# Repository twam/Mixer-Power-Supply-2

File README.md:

Mixer-Power-Supply-2
===

This repository is part of the USB audio mixer project described on https://www.twam.info/general/building-a-custom-usb-audio-mixer.

It supersedes http://github.com/twam/Mixer-Power-Supply.

## License

[![CC BY-SA 4.0][cc-by-sa-shield]][cc-by-sa]

This work is licensed under a [Creative Commons Attribution-NonCommercial-ShareAlike 4.0 International License][cc-by-sa].

[![CC BY-SA 4.0][cc-by-sa-image]][cc-by-sa]

[cc-by-sa]: http://creativecommons.org/licenses/by-nc-sa/4.0/
[cc-by-sa-image]: https://licensebuttons.net/l/by-nc-sa/4.0/88x31.png
[cc-by-sa-shield]: https://img.shields.io/badge/License-CC%20BY--NC--SA%204.0-lightgrey.svg

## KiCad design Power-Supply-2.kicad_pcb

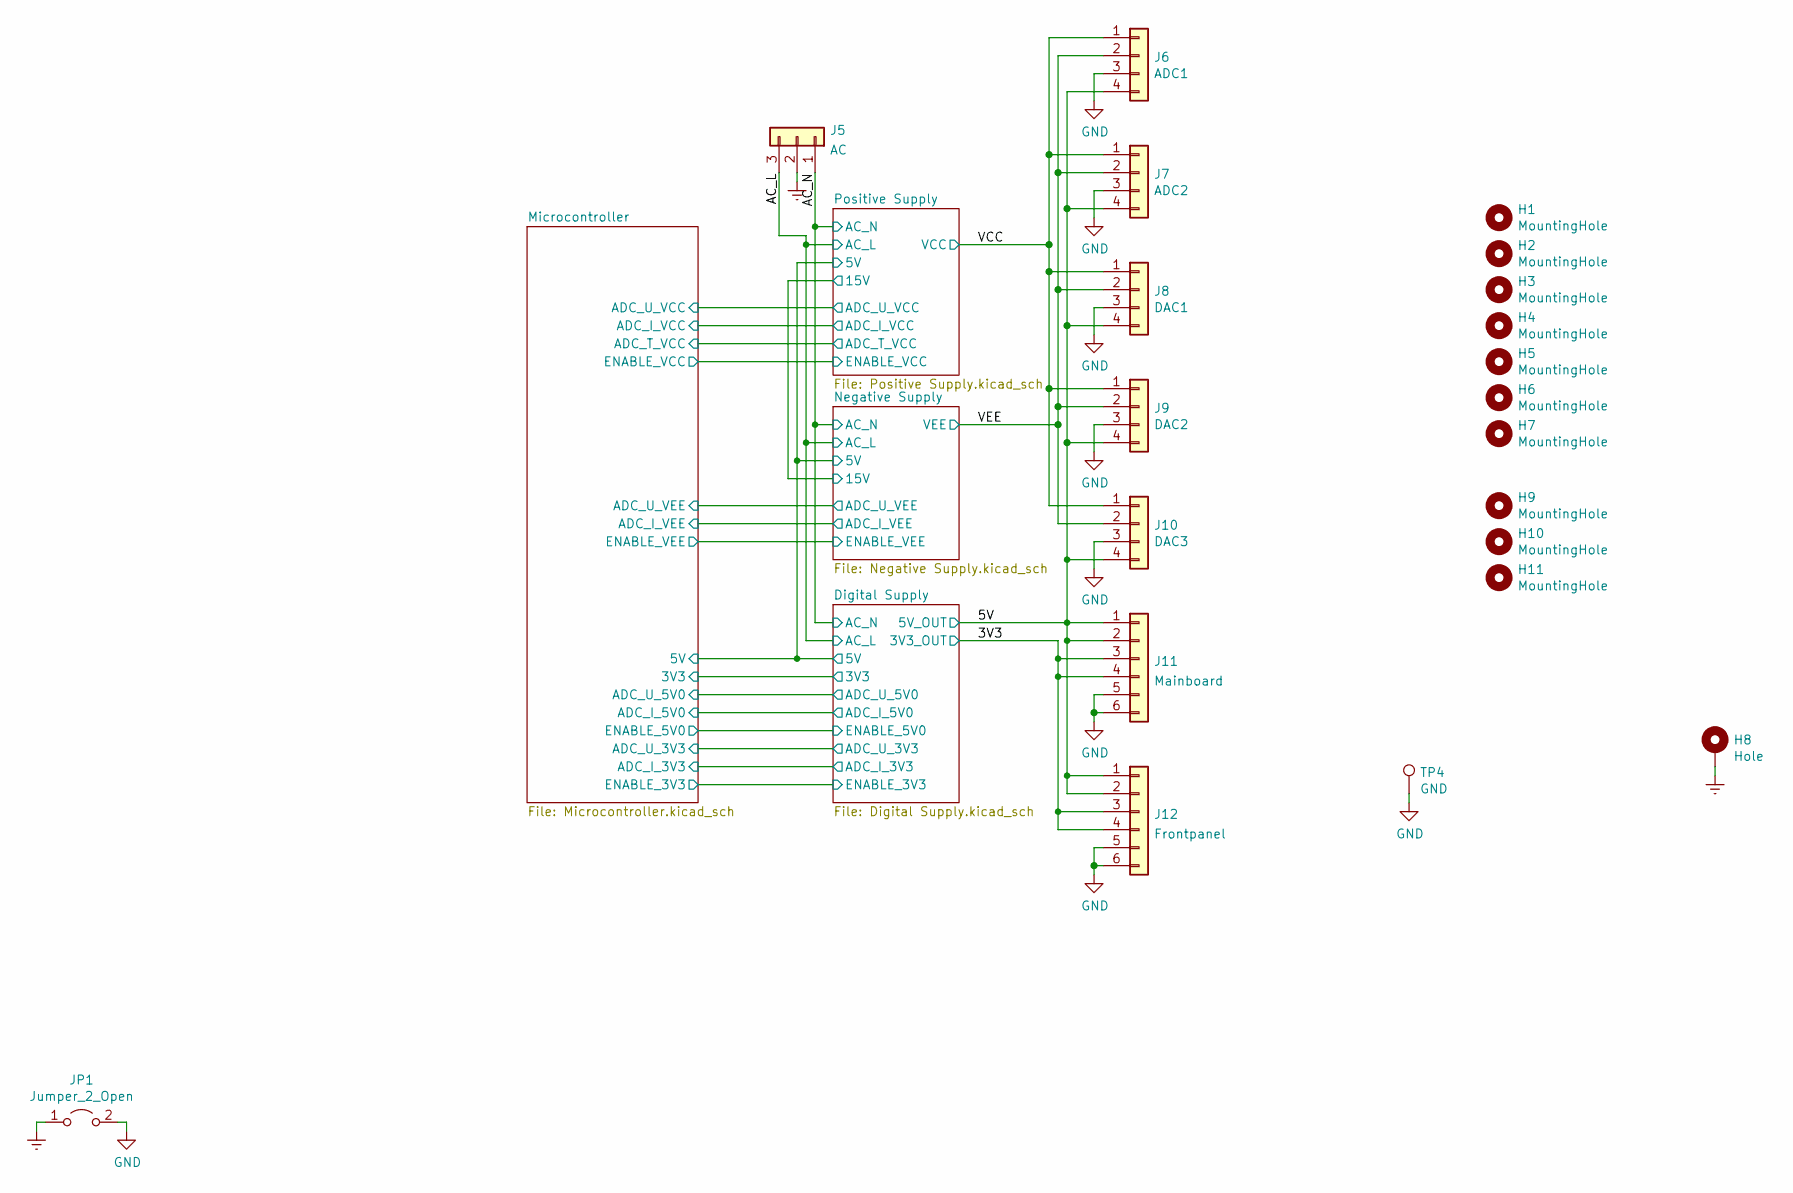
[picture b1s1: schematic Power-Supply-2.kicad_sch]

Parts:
H1, H2, H3, H4, H5, H6, H7: MountingHole; MountingHole_3.2mm_M3_DIN965
H8: Hole; MountingHole_3.2mm_M3_DIN965_Pad
H9, H10, H11: MountingHole; MountingHole_JLCPCB
J5: AC; JST_VH_B3P-VH_1x03_P3.96mm_Vertical
J6: ADC1; JST_VH_B4P-VH_1x04_P3.96mm_Vertical
J7: ADC2; JST_VH_B4P-VH_1x04_P3.96mm_Vertical
J8: DAC1; JST_VH_B4P-VH_1x04_P3.96mm_Vertical
J9: DAC2; JST_VH_B4P-VH_1x04_P3.96mm_Vertical
J10: DAC3; JST_VH_B4P-VH_1x04_P3.96mm_Vertical
J11: Mainboard; JST_VH_B6P-VH_1x06_P3.96mm_Vertical
J12: Frontpanel; JST_VH_B6P-VH_1x06_P3.96mm_Vertical
JP1: Jumper_2_Open; SolderJumper-2_P1.3mm_Open_RoundedPad1.0x1.5mm
TP4: GND; TestPoint_Pad_D2.0mm

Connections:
/3V3: J11.3, J11.4, J12.3, J12.4; also elsewhere on the board
/5V: J6.4, J7.4, J8.4, J9.4, J10.4, J11.1, J11.2, J12.1, J12.2; also elsewhere on the board
/AC_L: J5.3; also elsewhere on the board
/AC_N: J5.1; also elsewhere on the board
/VCC: J6.1, J7.1, J8.1, J9.1, J10.1; also elsewhere on the board
/VEE: J6.2, J7.2, J8.2, J9.2, J10.2; also elsewhere on the board
Earth: H8.1, J5.2, JP1.1 (A)
GND: J6.3, J7.3, J8.3, J9.3, J10.3, J11.5, J11.6, J12.5, J12.6, JP1.2 (B), TP4.1; also elsewhere on the board

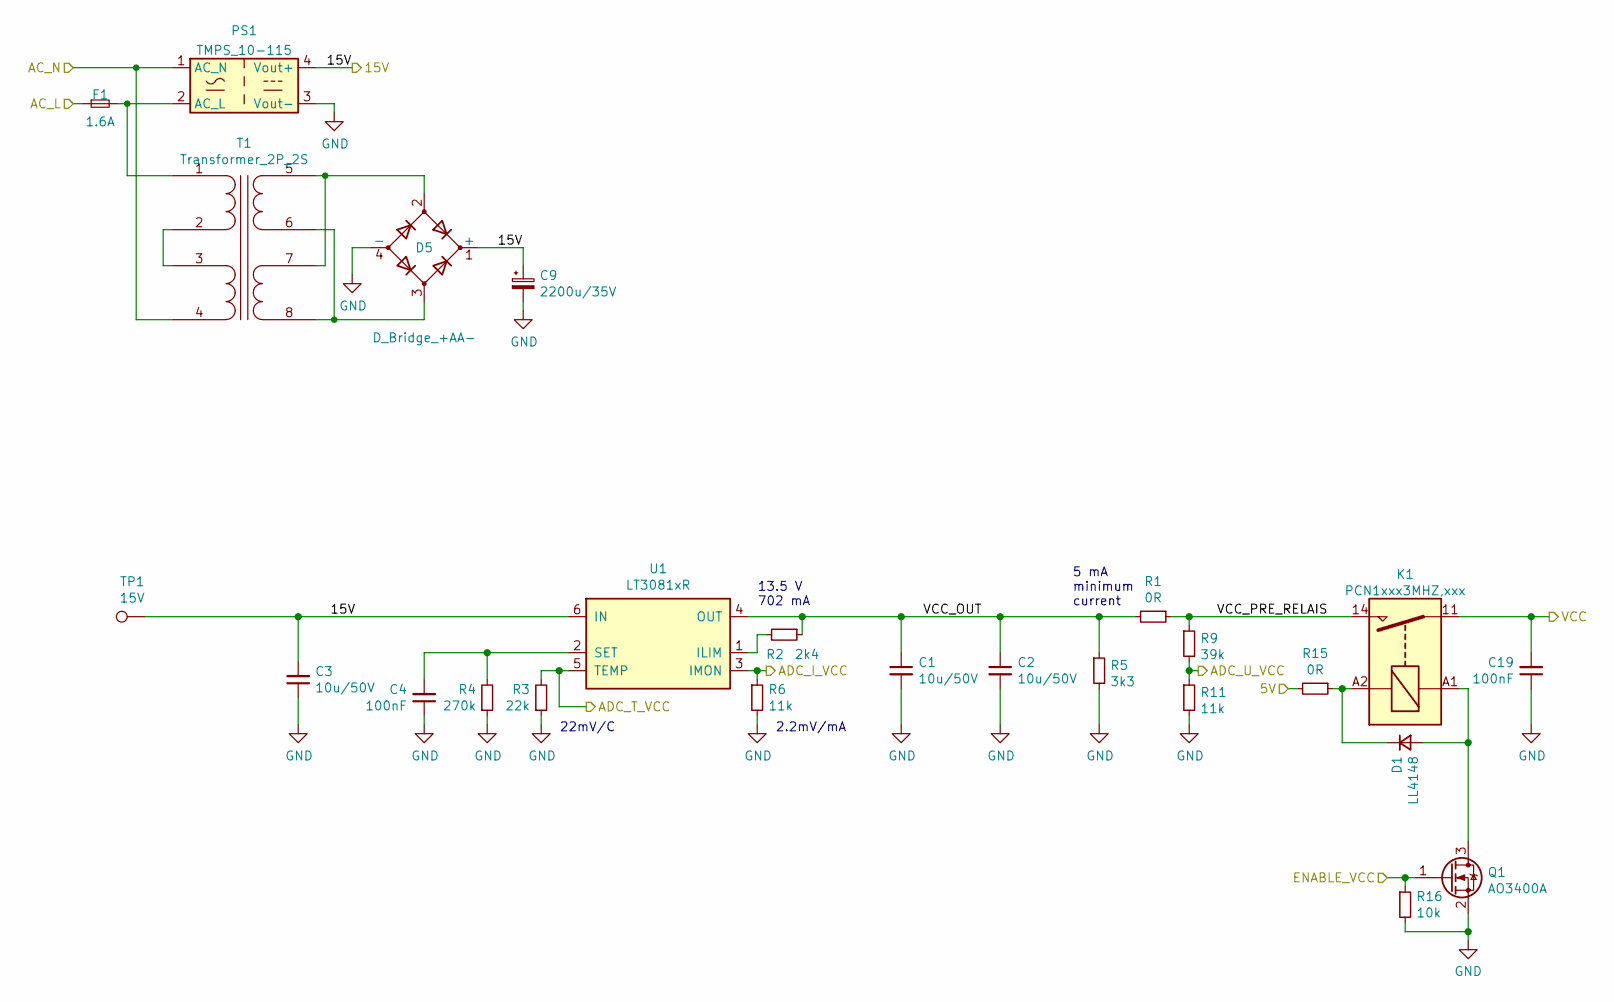
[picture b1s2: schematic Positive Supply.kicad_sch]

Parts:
C1, C2, C3: 10u/50V; C_1206_3216Metric; LCSC C13585
C4, C19: 100nF; C_0603_1608Metric; LCSC C14663
C9: 2200u/35V; CP_Radial_D16.0mm_P7.50mm
D1: LL4148; D_MiniMELF; LCSC C9808
D5: D_Bridge_+AA-; Diode_Bridge_Bourns_CD-HD2xxx
F1: 1.6A; Fuseholder_Cylinder-5x20mm_Schurter_0031_8201_Horizontal_Op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
K1: PCN1xxx3MHZ,xxx
PS1: TMPS_10-115; Converter_ACDC_TRACO_TMPS_10-xxx
Q1: AO3400A; TSOT-23; LCSC C20917
R1, R15: 0R; R_0805_2012Metric; LCSC C17477
R2: 2k4; R_0603_1608Metric; LCSC C22940
R3: 22k; R_0603_1608Metric; LCSC C31850
R4: 270k; R_0603_1608Metric; LCSC C22965
R5: 3k3; R_0805_2012Metric; LCSC C26010
R6, R11: 11k; R_0603_1608Metric; LCSC C25950
R9: 39k; R_0805_2012Metric; LCSC C23153
R16: 10k; R_0603_1608Metric; LCSC C25804
T1: Transformer_2P_2S; Talema_7xxxx_15VA
TP1: 15V; TestPoint_Pad_D2.0mm
U1: LT3081xR; TO-220-7_P2.54x3.8mm_StaggerOdd_Lead5.85mm_TabDown

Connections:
/AC_L: F1.1; also elsewhere on the board
/AC_N: PS1.1 (AC_N), T1.4 (OUT2B); also elsewhere on the board
/Digital Supply/5V: R15.2; also elsewhere on the board
/Microcontroller/ADC_I_VCC: R6.1, U1.3 (IMON); also elsewhere on the board
/Microcontroller/ADC_T_VCC: R3.2, U1.5 (TEMP); also elsewhere on the board
/Microcontroller/ADC_U_VCC: R9.2, R11.1; also elsewhere on the board
/Microcontroller/ENABLE_VCC: Q1.1 (G), R16.1; also elsewhere on the board
/Positive Supply/15V: C3.2, C9.1, D5.1 (+), PS1.4 (Vout+), TP1.1, U1.6 (IN); also elsewhere on the board
/Positive Supply/VCC_OUT: C1.1, C2.1, R1.2, R2.1, R5.1, U1.4 (OUT)
/Positive Supply/VCC_PRE_RELAIS: K1.14, R1.1, R9.1
/VCC: C19.2, K1.11; also elsewhere on the board
GND: C1.2, C2.2, C3.1, C4.1, C9.2, C19.1, D5.4 (-), PS1.3 (Vout-), Q1.2 (S), R3.1, R4.1, R5.2, R6.2, R11.2, R16.2; also elsewhere on the board
unnamed: C4.2, R4.2, U1.2 (SET)
unnamed: D1.1 (K), K1.A2, R15.1
unnamed: D1.2 (A), K1.A1, Q1.3 (D)
unnamed: D5.2, T1.5 (OUT1A), T1.7 (OUT2A)
unnamed: D5.3, T1.6 (OUT1B), T1.8 (OUT2B)
unnamed: F1.2, PS1.2 (AC_L), T1.1 (IN1A)
unnamed: R2.2, U1.1 (ILIM)
unnamed: T1.2 (IN1B), T1.3 (OUT2A)

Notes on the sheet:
2.2mV/mA
5 mA minimum current
22mV/C
13.5 V 702 mA

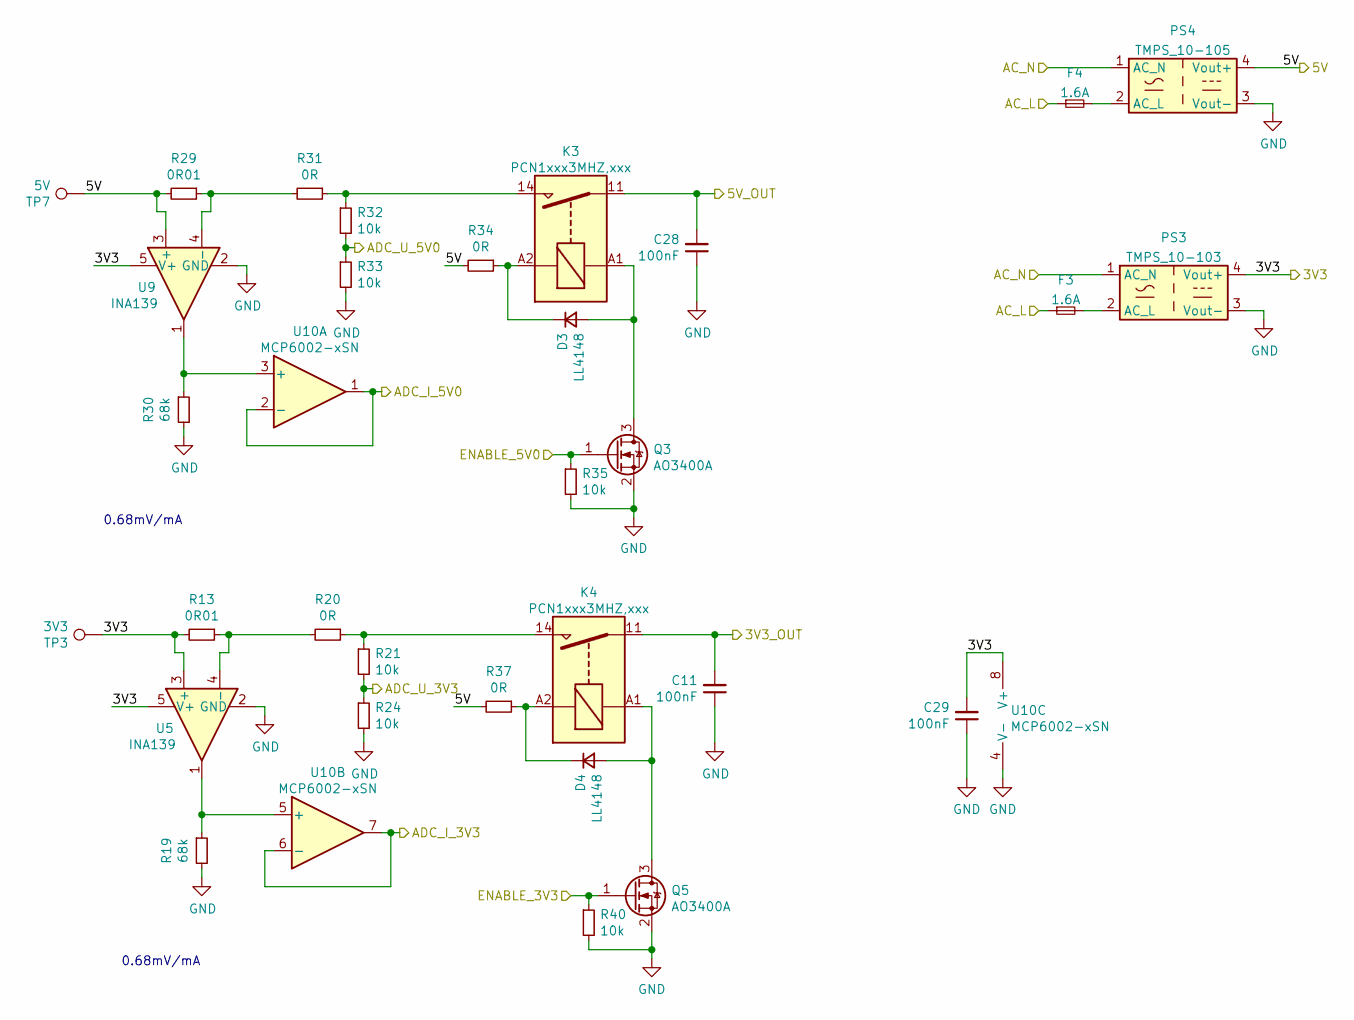
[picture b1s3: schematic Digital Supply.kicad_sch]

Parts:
C11, C28, C29: 100nF; C_0603_1608Metric; LCSC C14663
D3, D4: LL4148; D_MiniMELF; LCSC C9808
F3, F4: 1.6A; Fuseholder_Cylinder-5x20mm_Schurter_0031_8201_Horizontal_Op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
K3, K4: PCN1xxx3MHZ,xxx
PS3: TMPS_10-103; Converter_ACDC_TRACO_TMPS_10-xxx
PS4: TMPS_10-105; Converter_ACDC_TRACO_TMPS_10-xxx
Q3, Q5: AO3400A; TSOT-23; LCSC C20917
R13, R29: 0R01; R_1206_3216Metric; LCSC C308574
R19, R30: 68k; R_0603_1608Metric; LCSC C23231
R20, R31, R34, R37: 0R; R_0805_2012Metric; LCSC C17477
R21, R24, R32, R33, R35, R40: 10k; R_0603_1608Metric; LCSC C25804
TP3: 3V3; TestPoint_Pad_D2.0mm
TP7: 5V; TestPoint_Pad_D2.0mm
U5, U9: INA139; SOT-23-5; LCSC C129947
U10: MCP6002-xSN; SOIC-8_3.9x4.9mm_P1.27mm

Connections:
/3V3: C11.2, K4.11; also elsewhere on the board
/5V: C28.2, K3.11; also elsewhere on the board
/AC_L: F3.1, F4.1; also elsewhere on the board
/AC_N: PS3.1 (AC_N), PS4.1 (AC_N); also elsewhere on the board
/Digital Supply/3V3: C29.2, PS3.4 (Vout+), R13.2, TP3.1, U5.3 (+), U5.5 (V+), U9.5 (V+), U10.8 (V+); also elsewhere on the board
/Digital Supply/5V: PS4.4 (Vout+), R29.2, R34.2, R37.2, TP7.1, U9.3 (+); also elsewhere on the board
/Digital Supply/ADC_I_3V3: U10.6 (-), U10.7; also elsewhere on the board
/Digital Supply/ADC_I_5V0: U10.1, U10.2 (-); also elsewhere on the board
/Digital Supply/ADC_U_3V3: R21.2, R24.1; also elsewhere on the board
/Digital Supply/ADC_U_5V0: R32.2, R33.1; also elsewhere on the board
/Digital Supply/ENABLE_3V3: Q5.1 (G), R40.1; also elsewhere on the board
/Digital Supply/ENABLE_5V0: Q3.1 (G), R35.1; also elsewhere on the board
GND: C11.1, C28.1, C29.1, PS3.3 (Vout-), PS4.3 (Vout-), Q3.2 (S), Q5.2 (S), R19.2, R24.2, R30.2, R33.2, R35.2, R40.2, U5.2 (GND), U9.2 (GND), U10.4 (V-); also elsewhere on the board
unnamed: D3.1 (K), K3.A2, R34.1
unnamed: D3.2 (A), K3.A1, Q3.3 (D)
unnamed: D4.1 (K), K4.A2, R37.1
unnamed: D4.2 (A), K4.A1, Q5.3 (D)
unnamed: F3.2, PS3.2 (AC_L)
unnamed: F4.2, PS4.2 (AC_L)
unnamed: K3.14, R31.1, R32.1
unnamed: K4.14, R20.1, R21.1
unnamed: R13.1, R20.2, U5.4 (-)
unnamed: R19.1, U5.1, U10.5 (+)
unnamed: R29.1, R31.2, U9.4 (-)
unnamed: R30.1, U9.1, U10.3 (+)

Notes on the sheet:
0.68mV/mA

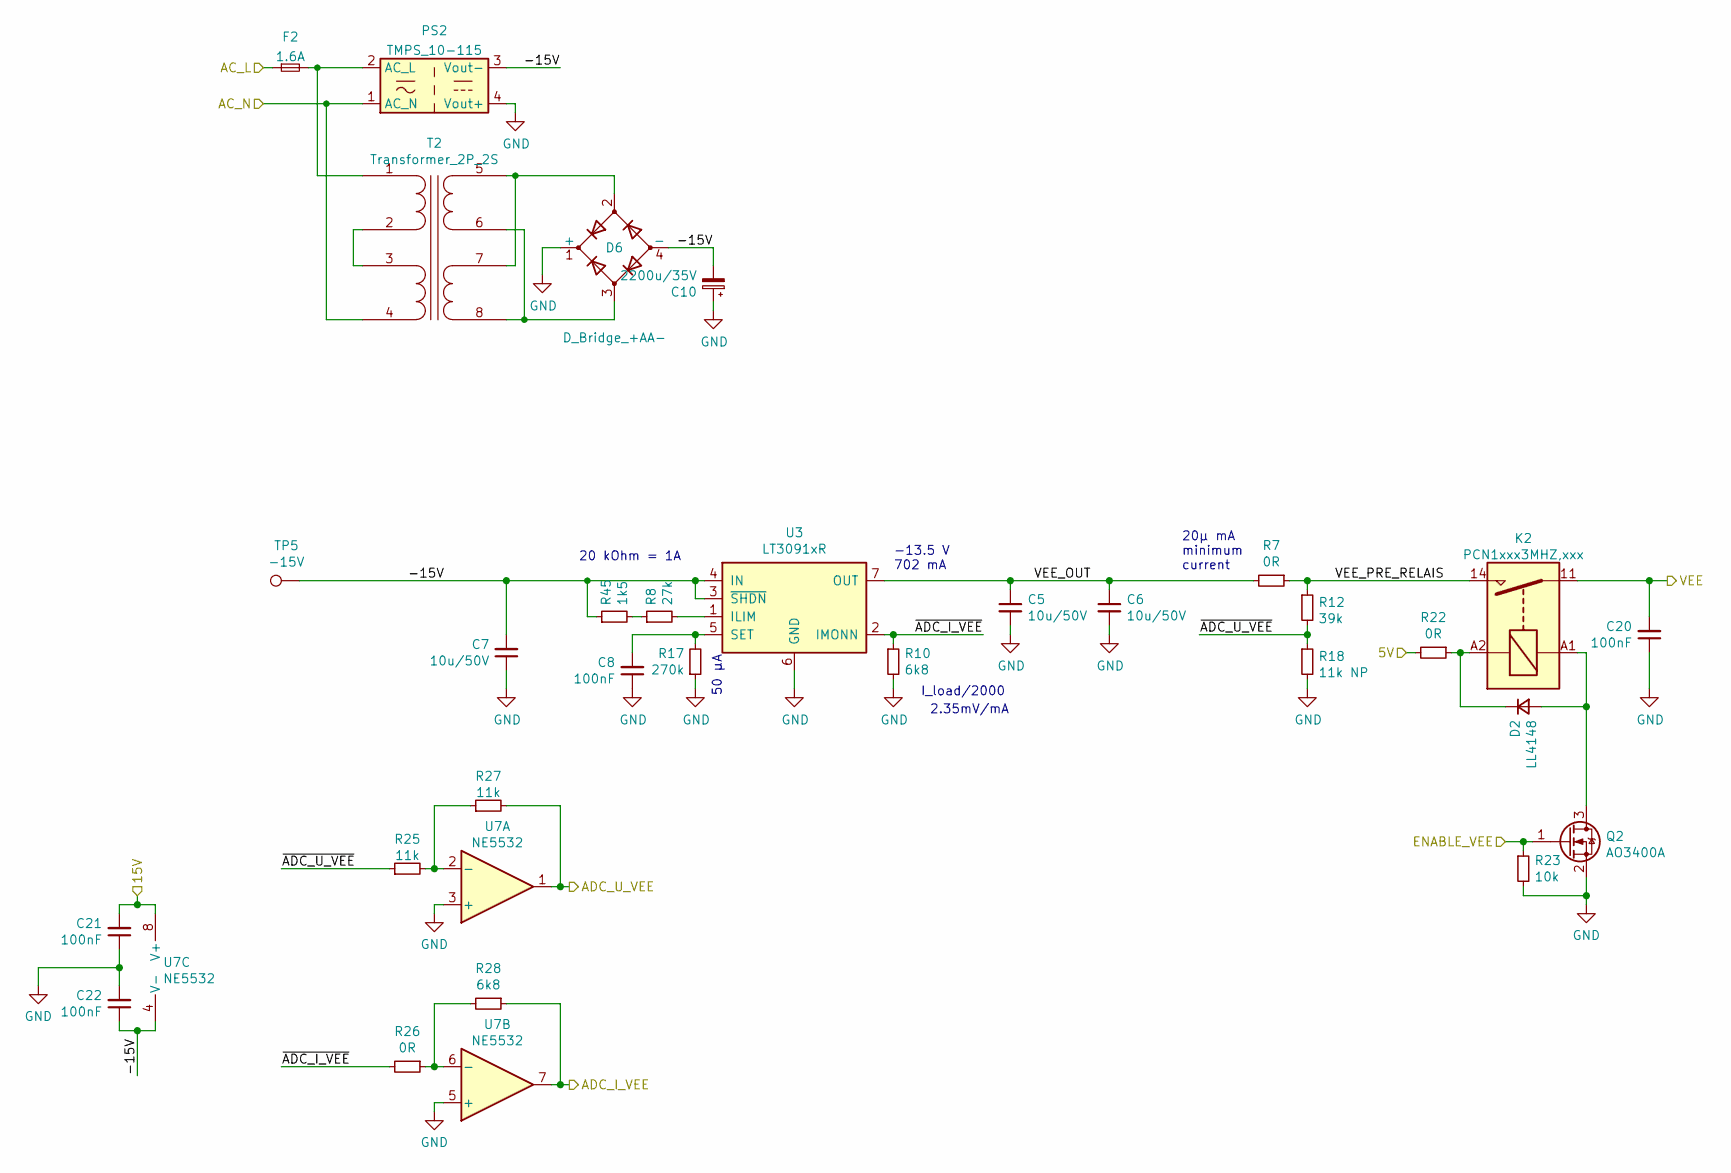
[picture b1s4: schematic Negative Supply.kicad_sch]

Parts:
C5, C6, C7: 10u/50V; C_1206_3216Metric; LCSC C13585
C8, C20, C21, C22: 100nF; C_0603_1608Metric; LCSC C14663
C10: 2200u/35V; CP_Radial_D16.0mm_P7.50mm
D2: LL4148; D_MiniMELF; LCSC C9808
D6: D_Bridge_+AA-; Diode_Bridge_Bourns_CD-HD2xxx
F2: 1.6A; Fuseholder_Cylinder-5x20mm_Schurter_0031_8201_Horizontal_Op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
K2: PCN1xxx3MHZ,xxx
PS2: TMPS_10-115; Converter_ACDC_TRACO_TMPS_10-xxx
Q2: AO3400A; TSOT-23; LCSC C20917
R7, R22, R26: 0R; R_0805_2012Metric; LCSC C17477
R8: 27k; R_0603_1608Metric; LCSC C22967
R10, R28: 6k8; R_0603_1608Metric; LCSC C23212
R12: 39k; R_0603_1608Metric; LCSC C23153
R17: 270k; R_0603_1608Metric; LCSC C22965
R18: 11k NP; R_0603_1608Metric
R23: 10k; R_0603_1608Metric; LCSC C25804
R25, R27: 11k; R_0603_1608Metric; LCSC C25950
R45: 1k5; R_0603_1608Metric; LCSC C22843
T2: Transformer_2P_2S; Talema_7xxxx_15VA
TP5: -15V; TestPoint_Pad_D2.0mm
U3: LT3091xR; TO-220-7_P2.54x3.8mm_StaggerOdd_Lead5.85mm_TabDown
U7: NE5532; SOIC-8_3.9x4.9mm_P1.27mm

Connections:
/AC_L: F2.1; also elsewhere on the board
/AC_N: PS2.1 (AC_N), T2.4 (OUT2B); also elsewhere on the board
/Digital Supply/5V: R22.2; also elsewhere on the board
/Microcontroller/ADC_I_VEE: R28.1, U7.7; also elsewhere on the board
/Microcontroller/ADC_U_VEE: R27.2, U7.1; also elsewhere on the board
/Microcontroller/ENABLE_VEE: Q2.1 (G), R23.1; also elsewhere on the board
/Negative Supply/-15V: C7.2, C10.2, C22.1, D6.4 (-), PS2.3 (Vout-), R45.1, TP5.1, U3.3 (~SHDN), U3.4 (IN), U7.4 (V-)
/Negative Supply/VEE_OUT: C5.1, C6.1, R7.2, U3.7 (OUT)
/Negative Supply/VEE_PRE_RELAIS: K2.14, R7.1, R12.1
/Negative Supply/~ADC_I_VEE: R10.1, R26.2, U3.2 (IMONN)
/Negative Supply/~ADC_U_VEE: R12.2, R18.1, R25.1
/Positive Supply/15V: C21.2, U7.8 (V+); also elsewhere on the board
/VEE: C20.2, K2.11; also elsewhere on the board
GND: C5.2, C6.2, C7.1, C8.1, C10.1, C20.1, C21.1, C22.2, D6.1 (+), PS2.4 (Vout+), Q2.2 (S), R10.2, R17.1, R18.2, R23.2, U3.6 (GND), U7.3 (+), U7.5 (+); also elsewhere on the board
unnamed: C8.2, R17.2, U3.5 (SET)
unnamed: D2.1 (K), K2.A2, R22.1
unnamed: D2.2 (A), K2.A1, Q2.3 (D)
unnamed: D6.2, T2.5 (OUT1A), T2.7 (OUT2A)
unnamed: D6.3, T2.6 (OUT1B), T2.8 (OUT2B)
unnamed: F2.2, PS2.2 (AC_L), T2.1 (IN1A)
unnamed: R8.1, R45.2
unnamed: R8.2, U3.1 (ILIM)
unnamed: R25.2, R27.1, U7.2 (-)
unnamed: R26.1, R28.2, U7.6 (-)
unnamed: T2.2 (IN1B), T2.3 (OUT2A)

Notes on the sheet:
20µ mA minimum current
20 kOhm = 1A
I_load/2000
50 µA
2.35mV/mA
-13.5 V 702 mA

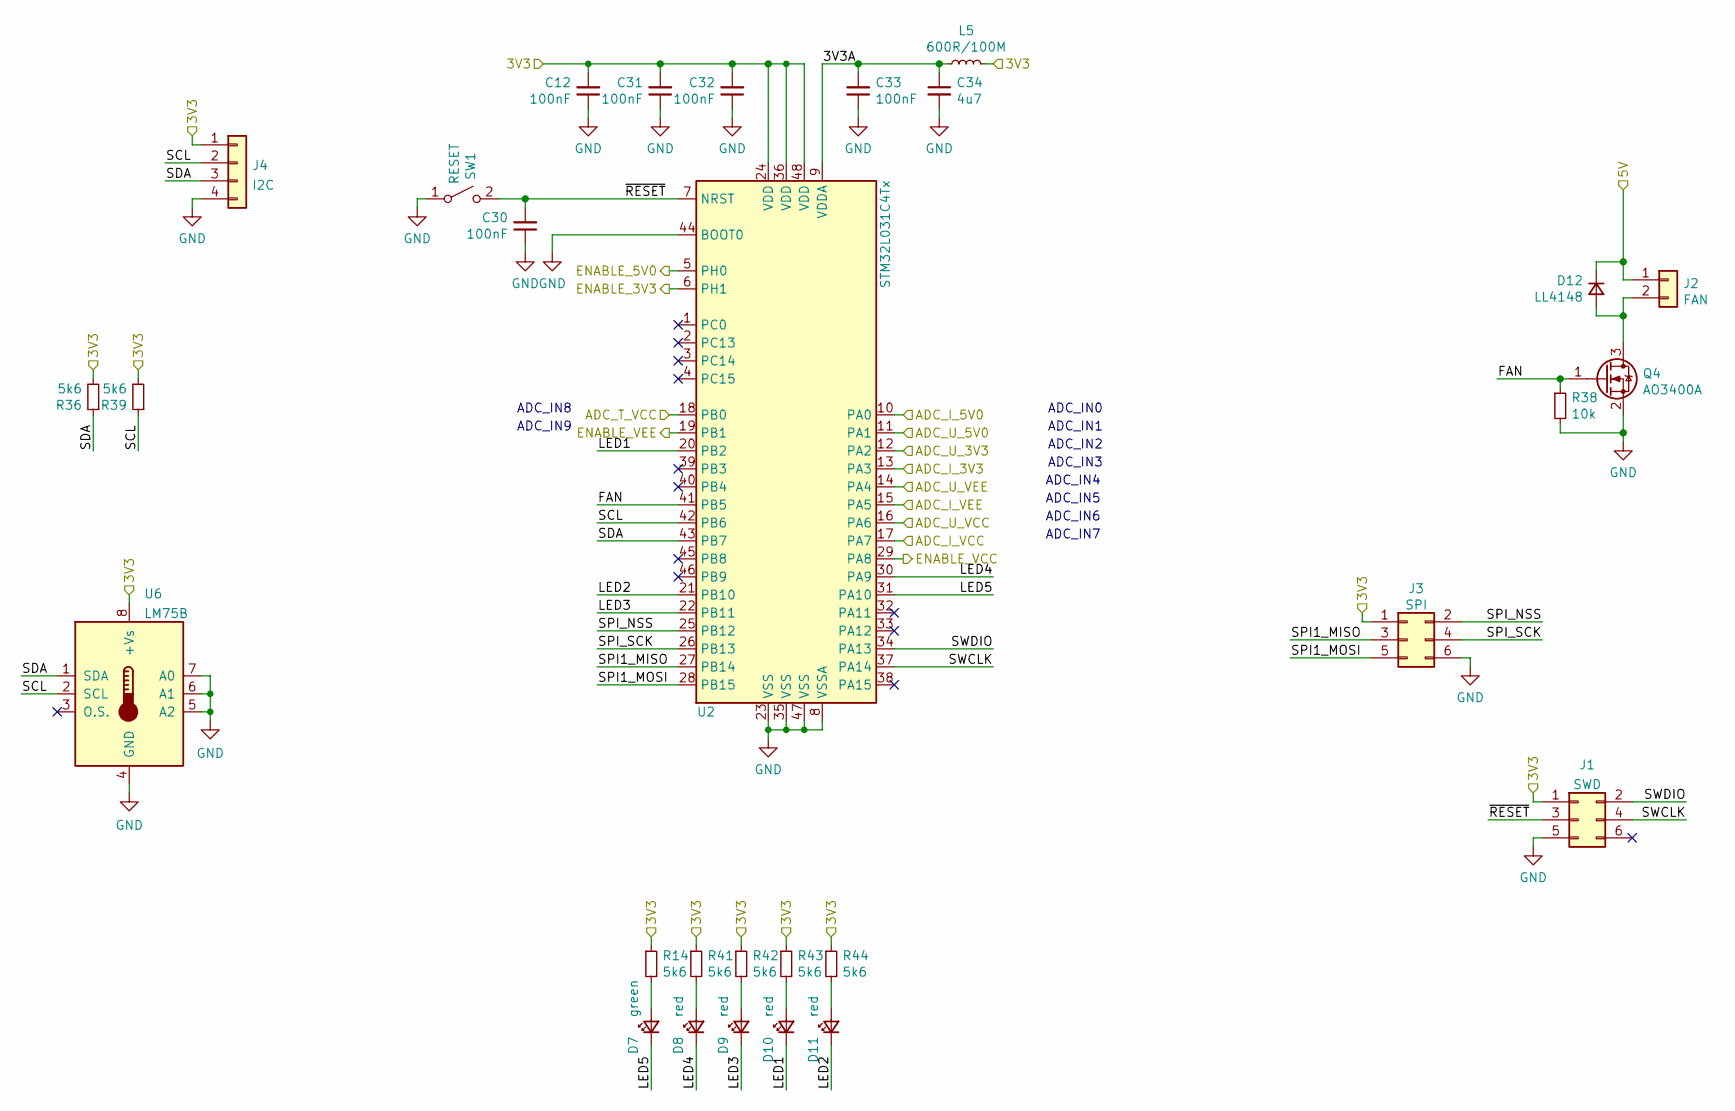
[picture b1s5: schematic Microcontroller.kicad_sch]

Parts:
C12, C30, C31, C32, C33: 100nF; C_0603_1608Metric; LCSC C14663
C34: 4u7; C_0805_2012Metric; LCSC C1779
D7: green; LED_0603_1608Metric; LCSC C72043
D8, D9, D10, D11: red; LED_0603_1608Metric; LCSC C2286
D12: LL4148; D_MiniMELF; LCSC C9808
J1: SWD; PinHeader_2x03_P2.54mm_Vertical
J2: FAN; Molex_KK-254_AE-6410-02A_1x02_P2.54mm_Vertical
J3: SPI; PinHeader_2x03_P2.54mm_Vertical
J4: I2C; PinHeader_1x04_P2.54mm_Vertical
L5: 600R/100M; L_0805_2012Metric; LCSC C1017
Q4: AO3400A; TSOT-23; LCSC C20917
R14, R36, R39, R41, R42, R43, R44: 5k6; R_0603_1608Metric; LCSC C23189
R38: 10k; R_0603_1608Metric; LCSC C25804
SW1: RESET; SW_SPST_B3U-1000P; LCSC C231329
U2: STM32L031C4Tx; LQFP-48_7x7mm_P0.5mm
U6: LM75B; SOIC-8_3.9x4.9mm_P1.27mm

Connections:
/Digital Supply/3V3: C12.2, C31.2, C32.2, J1.1, J3.1, J4.1, L5.2, R14.1, R36.2, R39.2, R41.1, R42.1, R43.1, R44.1, U2.24 (VDD), U2.36 (VDD), U2.48 (VDD), U6.8 (+Vs); also elsewhere on the board
/Digital Supply/5V: D12.1 (K), J2.1; also elsewhere on the board
/Digital Supply/ADC_I_3V3: U2.13 (PA3); also elsewhere on the board
/Digital Supply/ADC_I_5V0: U2.10 (PA0); also elsewhere on the board
/Digital Supply/ADC_U_3V3: U2.12 (PA2); also elsewhere on the board
/Digital Supply/ADC_U_5V0: U2.11 (PA1); also elsewhere on the board
/Digital Supply/ENABLE_3V3: U2.6 (PH1); also elsewhere on the board
/Digital Supply/ENABLE_5V0: U2.5 (PH0); also elsewhere on the board
/Microcontroller/3V3A: C33.2, C34.1, L5.1, U2.9 (VDDA)
/Microcontroller/ADC_I_VCC: U2.17 (PA7); also elsewhere on the board
/Microcontroller/ADC_I_VEE: U2.15 (PA5); also elsewhere on the board
/Microcontroller/ADC_T_VCC: U2.18 (PB0); also elsewhere on the board
/Microcontroller/ADC_U_VCC: U2.16 (PA6); also elsewhere on the board
/Microcontroller/ADC_U_VEE: U2.14 (PA4); also elsewhere on the board
/Microcontroller/ENABLE_VCC: U2.29 (PA8); also elsewhere on the board
/Microcontroller/ENABLE_VEE: U2.19 (PB1); also elsewhere on the board
/Microcontroller/FAN: Q4.1 (G), R38.1, U2.41 (PB5)
/Microcontroller/LED1: D10.1 (K), U2.20 (PB2)
/Microcontroller/LED2: D11.1 (K), U2.21 (PB10)
/Microcontroller/LED3: D9.1 (K), U2.22 (PB11)
/Microcontroller/LED4: D8.1 (K), U2.30 (PA9)
/Microcontroller/LED5: D7.1 (K), U2.31 (PA10)
/Microcontroller/SCL: J4.2, R39.1, U2.42 (PB6), U6.2 (SCL)
/Microcontroller/SDA: J4.3, R36.1, U2.43 (PB7), U6.1 (SDA)
/Microcontroller/SPI1_MISO: J3.3, U2.27 (PB14)
/Microcontroller/SPI1_MOSI: J3.5, U2.28 (PB15)
/Microcontroller/SPI_NSS: J3.2, U2.25 (PB12)
/Microcontroller/SPI_SCK: J3.4, U2.26 (PB13)
/Microcontroller/SWCLK: J1.4, U2.37 (PA14)
/Microcontroller/SWDIO: J1.2, U2.34 (PA13)
/Microcontroller/~RESET: C30.2, J1.3, SW1.2 (B), U2.7 (NRST)
GND: C12.1, C30.1, C31.1, C32.1, C33.1, C34.2, J1.5, J3.6, J4.4, Q4.2 (S), R38.2, SW1.1 (A), U2.8 (VSSA), U2.23 (VSS), U2.35 (VSS), U2.44 (BOOT0), U2.47 (VSS), U6.4 (GND), U6.5 (A2), U6.6 (A1), U6.7 (A0); also elsewhere on the board
unnamed: D7.2 (A), R14.2
unnamed: D8.2 (A), R41.2
unnamed: D9.2 (A), R42.2
unnamed: D10.2 (A), R43.2
unnamed: D11.2 (A), R44.2
unnamed: D12.2 (A), J2.2, Q4.3 (D)

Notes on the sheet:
ADC_IN7
ADC_IN6
ADC_IN3
ADC_IN4
ADC_IN5
ADC_IN0
ADC_IN8
ADC_IN9
ADC_IN2
ADC_IN1

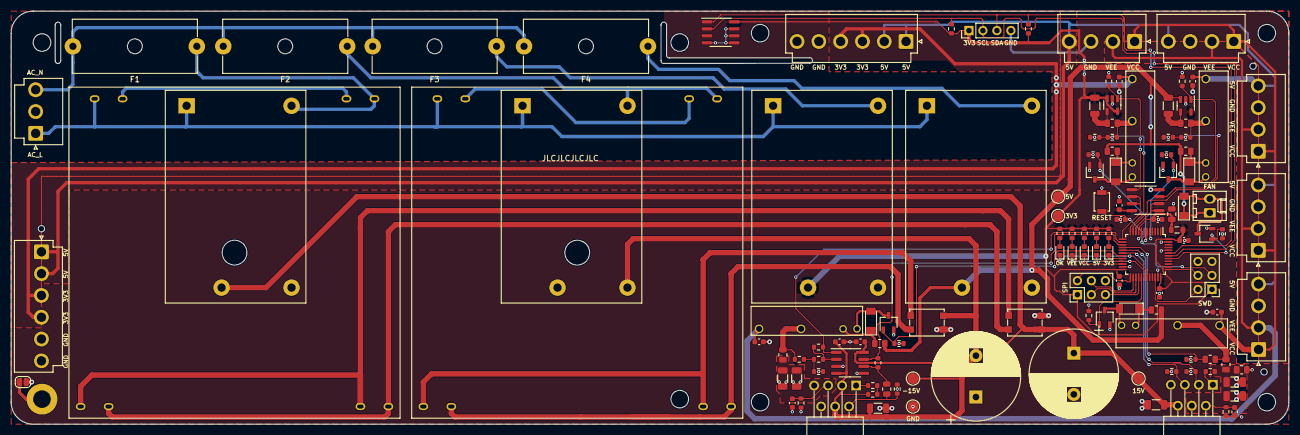
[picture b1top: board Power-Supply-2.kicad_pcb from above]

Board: 2 copper layers, 232.0 x 75.0 mm, 138 parts (0 on the bottom side), 84 nets.

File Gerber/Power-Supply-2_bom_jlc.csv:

"Comment","Designator","Footprint","LCSC Part #"
"10u/50V","C1,C2,C3,C5,C6,C7","C_1206_3216Metric","C13585"
"100nF","C4,C19,C8,C20,C21,C22,C11,C28,C29,C12,C30,C31,C32,C33","C_0603_1608Metric","C14663"
"4u7","C34","C_0805_2012Metric","C1779"
"LL4148","D1,D2,D3,D4,D12","D_MiniMELF","C9808"
"green","D7","LED_0603_1608Metric","C72043"
"red","D8,D9,D10,D11","LED_0603_1608Metric","C2286"
"600R/100M","L5","L_0805_2012Metric","C1017"
"AO3400A","Q1,Q2,Q3,Q5,Q4","TSOT-23","C20917"
"0R","R1,R15,R7,R22,R26,R20,R31,R34,R37","R_0805_2012Metric","C17477"
"2k4","R2","R_0603_1608Metric","C22940"
"22k","R3","R_0603_1608Metric","C31850"
"270k","R4,R17","R_0603_1608Metric","C22965"
"3k3","R5","R_0805_2012Metric","C26010"
"11k","R6,R11,R25,R27","R_0603_1608Metric","C25950"
"27k","R8","R_0603_1608Metric","C22967"
"39k","R9","R_0805_2012Metric","C23153"
"6k8","R10,R28","R_0603_1608Metric","C23212"
"39k","R12","R_0603_1608Metric","C23153"
"0R01","R13,R29","R_1206_3216Metric","C308574"
"5k6","R14,R36,R39,R41,R42,R43,R44","R_0603_1608Metric","C23189"
"10k","R16,R23,R21,R24,R32,R33,R35,R40,R38","R_0603_1608Metric","C25804"
"68k","R19,R30","R_0603_1608Metric","C23231"
"1k5","R45","R_0603_1608Metric","C22843"
"RESET","SW1","SW_SPST_B3U-1000P","C231329"
"INA139","U5,U9","SOT-23-5","C129947"
"NE5532","U7","SOIC-8_3.9x4.9mm_P1.27mm","C7426"
"MCP6002-xSN","U10","SOIC-8_3.9x4.9mm_P1.27mm","C7377"

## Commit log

2022-01-16 Initial commit. Rev1
